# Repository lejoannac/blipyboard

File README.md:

# blipyboard
An 8 key macropad with an OLED screen and potentiometer for HackPad. It also has 8 SK6812 leds for lighting and utilizes custom KMK firmware.

# **CAD Model**
<br>
Designed and Modeled using Fusion 360

# **Schematic**

# **PCB**
<br>
Schematic and PCB created using KiCad

# **BOM**
8x Cherry MX Switches<br>
9x 1N4148 Diodes<br>
8x SK6812 Mini LED<br>
8x Keycaps<br>
1x Rotary Encoder with push button<br>
1x 0.91" OLED Display (128x32)<br>
1x XIAO-RP2040 microcontroller<br>
4x M3x10mm screws<br>
1x Custom PCB<br>
1x 1kg spool of white filament from Amazon<br>
I will print my own case

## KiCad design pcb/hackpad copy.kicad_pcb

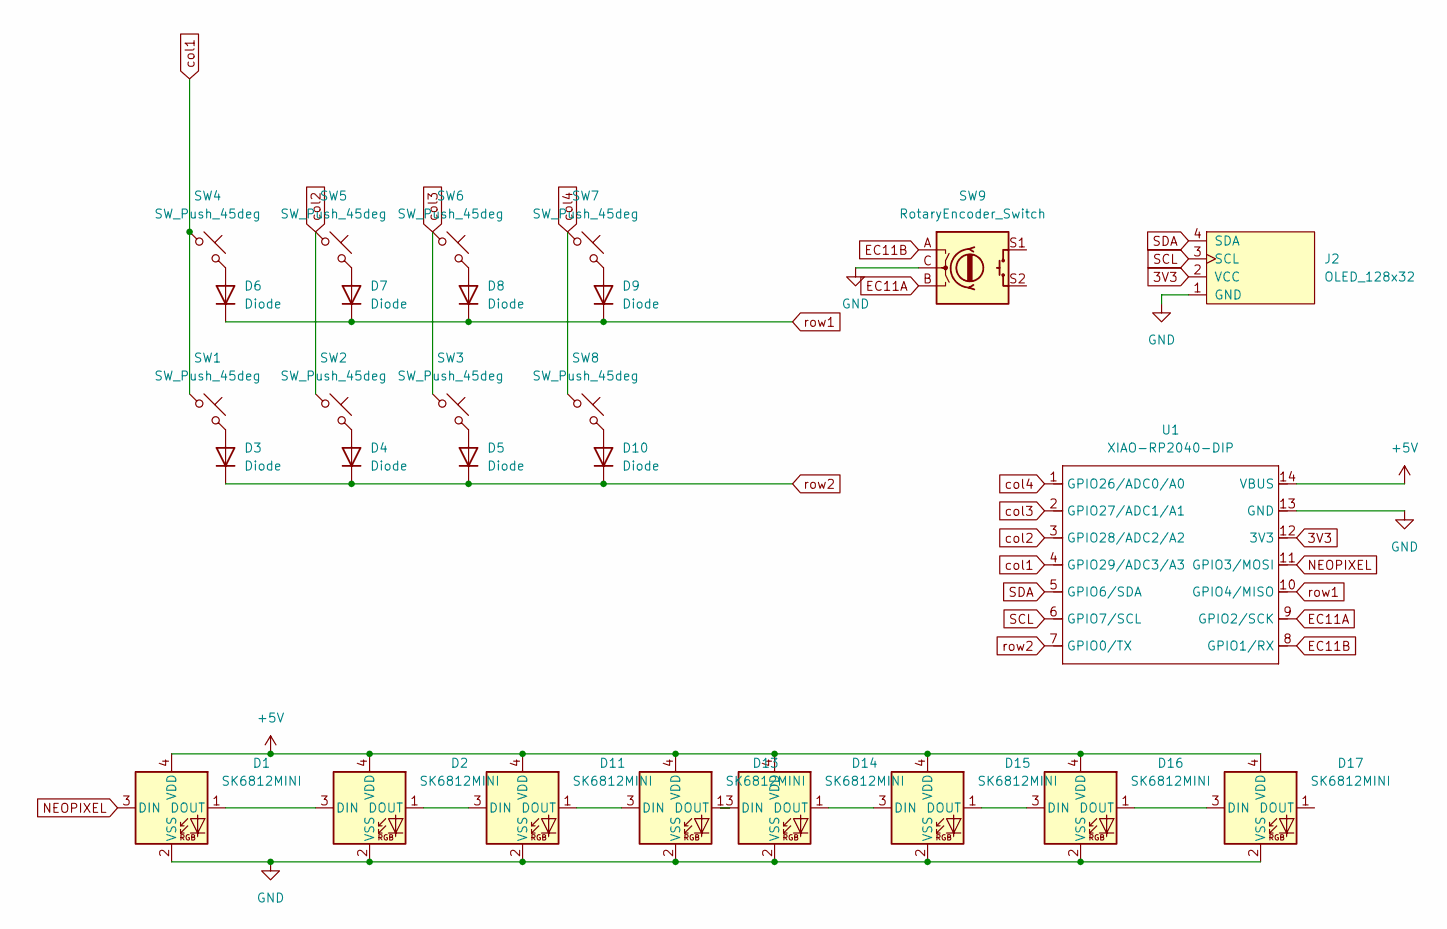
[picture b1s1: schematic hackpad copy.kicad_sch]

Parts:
D1, D2, D11, D13, D14, D15, D16, D17: SK6812MINI; LED_SK6812MINI_PLCC4_3.5x3.5mm_P1.75mm
D3, D4, D5, D6, D7, D8, D9, D10: Diode; D_DO-35_SOD27_P7.62mm_Horizontal
J2: OLED_128x32
SW1, SW2, SW3, SW4, SW5, SW6, SW7, SW8: SW_Push_45deg; SW_Cherry_MX_1.00u_PCB
SW9: RotaryEncoder_Switch; RotaryEncoder_Alps_EC11E-Switch_Vertical_H20mm
U1: XIAO-RP2040-DIP

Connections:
3V3: J2.2 (VCC), U1.12 (3V3)
+5V: D1.4 (VDD), D2.4 (VDD), D11.4 (VDD), D13.4 (VDD), D14.4 (VDD), D15.4 (VDD), D16.4 (VDD), D17.4 (VDD), U1.14 (VBUS)
EC11A: SW9.B, U1.9 (GPIO2/SCK)
EC11B: SW9.A, U1.8 (GPIO1/RX)
GND: D1.2 (VSS), D2.2 (VSS), D11.2 (VSS), D13.2 (VSS), D14.2 (VSS), D15.2 (VSS), D16.2 (VSS), D17.2 (VSS), J2.1 (GND), SW9.C, U1.13 (GND)
NEOPIXEL: D1.3 (DIN), U1.11 (GPIO3/MOSI)
unnamed: D1.1 (DOUT), D2.3 (DIN)
unnamed: D3.2 (A), SW1.2
unnamed: D4.2 (A), SW2.2
unnamed: D5.2 (A), SW3.2
unnamed: D6.2 (A), SW4.2
unnamed: D7.2 (A), SW5.2
unnamed: D8.2 (A), SW6.2
unnamed: D9.2 (A), SW7.2
unnamed: D10.2 (A), SW8.2
unnamed: D2.1 (DOUT), D11.3 (DIN)
unnamed: D11.1 (DOUT), D13.3 (DIN)
unnamed: D13.1 (DOUT), D14.3 (DIN)
unnamed: D14.1 (DOUT), D15.3 (DIN)
unnamed: D15.1 (DOUT), D16.3 (DIN)
unnamed: D16.1 (DOUT), D17.3 (DIN)
SCL: J2.3 (SCL), U1.6 (GPIO7/SCL)
SDA: J2.4 (SDA), U1.5 (GPIO6/SDA)
col1: SW1.1, SW4.1, U1.4 (GPIO29/ADC3/A3)
col2: SW2.1, SW5.1, U1.3 (GPIO28/ADC2/A2)
col3: SW3.1, SW6.1, U1.2 (GPIO27/ADC1/A1)
col4: SW7.1, SW8.1, U1.1 (GPIO26/ADC0/A0)
row1: D6.1 (K), D7.1 (K), D8.1 (K), D9.1 (K), U1.10 (GPIO4/MISO)
row2: D3.1 (K), D4.1 (K), D5.1 (K), D10.1 (K), U1.7 (GPIO0/TX)

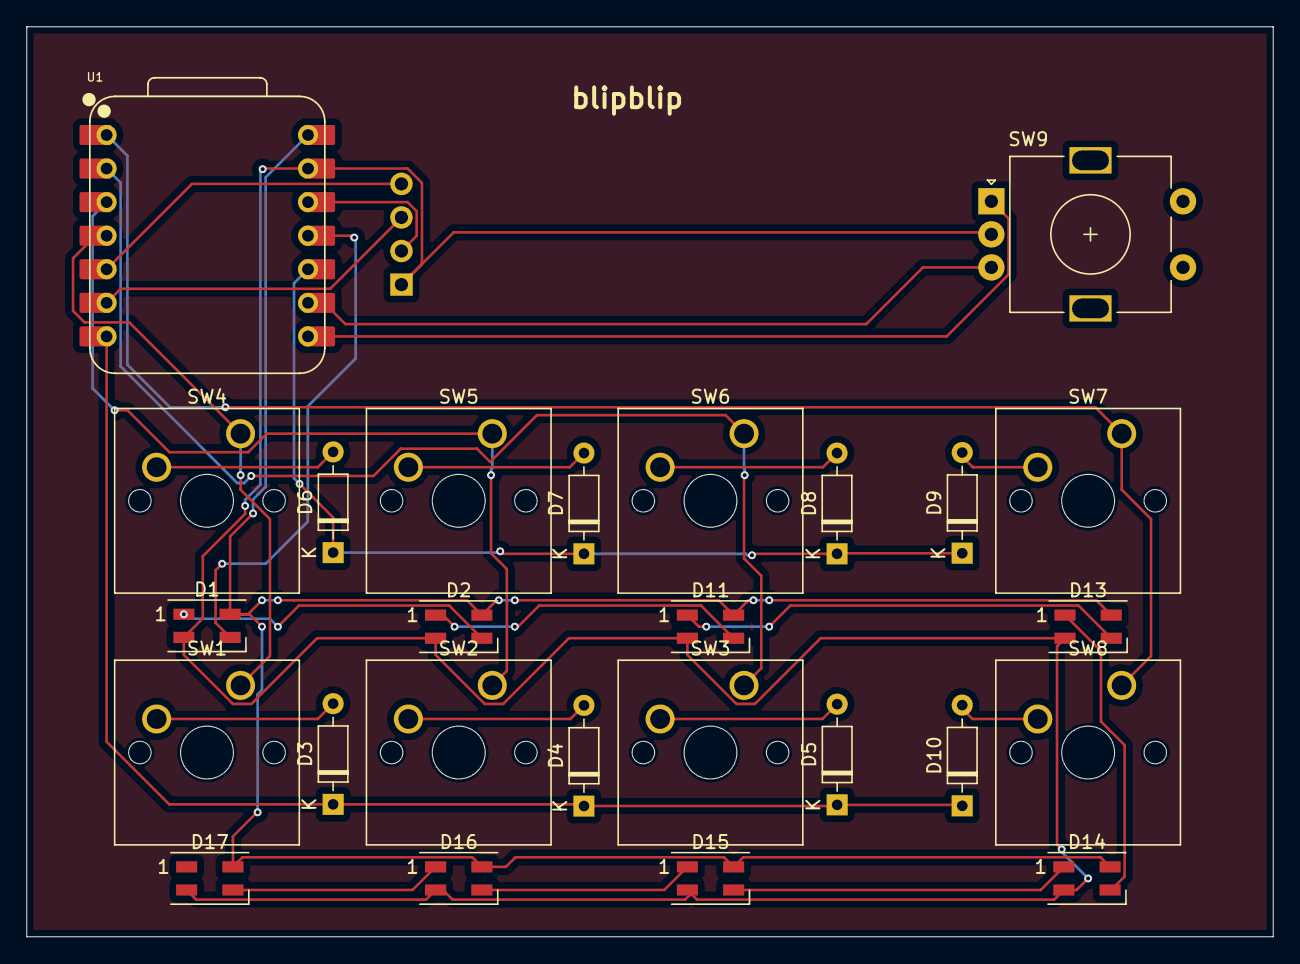
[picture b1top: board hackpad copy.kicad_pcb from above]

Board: 2 copper layers, 94.3 x 68.9 mm, 27 parts (0 on the bottom side), 29 nets.
